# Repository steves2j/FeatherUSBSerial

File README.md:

# Feather USB Serial Big Fat Switch Edition
*FT232 USB serial port connection to RX/TX (Serial1) in an Adafruit FeatherWing form-factor*

This simple board allows easy access to Serial1, typically for debugging purposes. You insert it in a [Adafruit FeatherWing Doubler](https://www.adafruit.com/product/2890) or [Tripler](https://www.adafruit.com/product/3417) along with your device.

While it's no big deal to attach a [FT232 breakout](https://www.sparkfun.com/products/12731), the FeatherWing is nice and neat with no dangling wires.
Now with Big fat Mode and Reset buttons. No more fiddling trying to reset and DFU that Particle.

This post has all of the information you need to build your own. It's not available for purchase pre-built.

## What You Need

This is a somewhat advanced project mainly because the FT232 has a lot of pins, very close together. It's probably not practical to solder by hand, so you'll need a SMD reflow oven to do it effectively.

- Circuit boards (I order them from [OshPark](https://oshpark.com))
- Stencil (this board can be assembled without one, but I order them from [OshStencils](https://oshstencils.com))
- Solder paste
- Reflow oven (the inexpensive [T962](https://www.amazon.com/dp/B01LZYEF90/ref=dp_prsubs_1) works fine)
- Soldering iron (for the header pins)
- Regular solder

In the eagle directory are the .brd and .sch files for Eagle CAD. One of the reasons I like OshPark is that they accept the .brd files directly, instead of having to generate Gerber files. It costs US$9.00 with free shipping for 3 FeatherWing boards.

There's also a .lbr file with all of the parts in this project.

## BOM (Bill of Materials)

| Quantity | Item | Example |
| --- | --- | --- |
| 1 | 0.01 uF capacitor 0805 | [SAMSUNG CL21B103KCANNNC](https://www.digikey.com/product-detail/en/samsung-electro-mechanics/CL21B103KCANNNC/1276-1249-6-ND/3891763) |
| 2 | 0.1 uF capacitor 0805 | [SAMSUNG CL21B104KBFNNNE](https://www.digikey.co.nz/product-detail/en/samsung-electro-mechanics/CL21B104KBFNNNE/1276-1180-1-ND/3889266) |
| 1 | 4.7 uF capacitor 0805 | [Murata GRM21BR61H475KE51L](https://www.digikey.co.nz/product-detail/en/murata-electronics-north-america/GRM21BR61H475KE51L/490-10751-1-ND/5251349) |
| 1 | Ferrite Bead 40 ohm 0805 | [Laird MI0805K400R-10](https://www.digikey.com/products/en/filters/ferrite-beads-and-chips/841?k=MI0805K400R&k=&pkeyword=MI0805K400R&sv=0&pv7=2&pv1989=0&sf=0&quantity=&ColumnSort=0&page=1&pageSize=25) |
| 3 | 680 ohm resistor 1/8w 0805 | [Panasonic ERJ-6GEYJ681V](https://www.digikey.com/product-detail/en/panasonic-electronic-components/ERJ-6GEYJ681V/P680ACT-ND/90033) | 
| 2 | LED red 5mA 0603 | [Lite-On LTST-C193KRKT-5A](https://www.digikey.com/product-detail/en/lite-on-inc/LTST-C193KRKT-5A/160-1830-1-ND/2356251) |
| 1 | LED green 5mA 0603 | [Lite-On LTST-C193KGKT-5A](https://www.digikey.com/product-detail/en/lite-on-inc/LTST-C193KGKT-5A/160-1828-1-ND/2356247) |
| 1 | FT232RL USB serial | [FTDI FT232RL](https://www.digikey.com/product-detail/en/ftdi-future-technology-devices-international-ltd/FT232RL-REEL/768-1007-1-ND/1836402) |
| 1 | Micro USB B SMD | [Amphenol FCI 10118194-0001LF](https://www.digikey.com/products/en?keywords=609-4618-1-nd) |
| | Male header pins 0.1" | [Sullins PRPC040SAAN-RC](https://www.digikey.com/product-detail/en/PRPC040SAAN-RC/S1011EC-40-ND/2775214) |
| 1 | Tactile Switch Red | [TL3300CF260Q](https://www.digikey.co.nz/product-detail/en/e-switch/TL3300CF260Q/EG4905CT-ND/2498465) |
| 1 | Tactile Switch Blk | [TL3300CF160Q](https://www.digikey.co.nz/product-detail/en/e-switch/TL3300CF160Q/EG4904CT-ND/2498463) |

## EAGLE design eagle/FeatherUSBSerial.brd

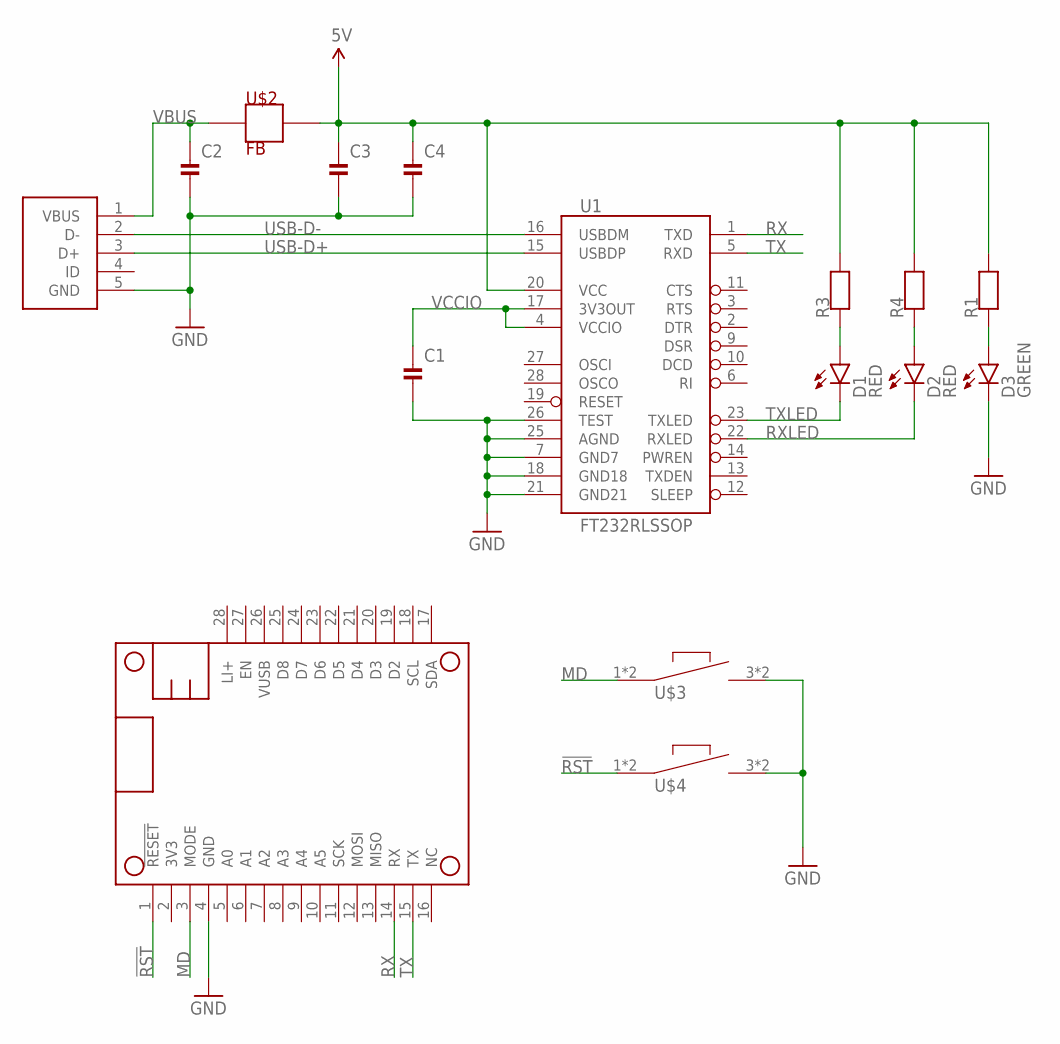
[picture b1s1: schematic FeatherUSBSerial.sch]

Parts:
C1, C3: 0.1uF; _0805MP
C2: 0.01uF; _0805MP
C4: 4.7uF; _0805MP
D1, D2: RED; LED-0603
D3: GREEN; LED-0603
MS1: FEATHERWING_NODIM
R1, R3, R4: 680; 0805-NO
U1: FT232RLSSOP; SSOP28DB
U$1: USB-MICRO-B-SOCKET-AMPHENOL; USB-B-SMT-AMPHENOL
U$2: FB; 0805
U$3, U$4: TL3300CFXXXQ; 12MM_TACTILE

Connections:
5V: C3.1, C4.1, R1.2, R3.2, R4.2, U1.20 (VCC), U$2.2
!RST: MS1.1 (!RESET), U$4.1, U$4.2
GND: C1.2, C2.2, C3.2, C4.2, D3.C, MS1.4 (GND), U1.7 (GND7), U1.18 (GND18), U1.21 (GND21), U1.25 (AGND), U1.26 (TEST), U$1.5 (GND), U$3.3, U$3.4, U$4.3, U$4.4
MD: MS1.3 (MODE), U$3.1, U$3.2
unnamed: D3.A, R1.1
unnamed: D1.A, R3.1
unnamed: D2.A, R4.1
RX: MS1.14 (RX), U1.1 (TXD)
RXLED: D2.C, U1.22 (RXLED)
TX: MS1.15 (TX), U1.5 (RXD)
TXLED: D1.C, U1.23 (TXLED)
USB-D+: U1.15 (USBDP), U$1.3 (D+)
USB-D-: U1.16 (USBDM), U$1.2 (D-)
VBUS: C2.1, U$1.1 (VBUS), U$2.1
VCCIO: C1.1, U1.4 (VCCIO), U1.17 (3V3OUT)

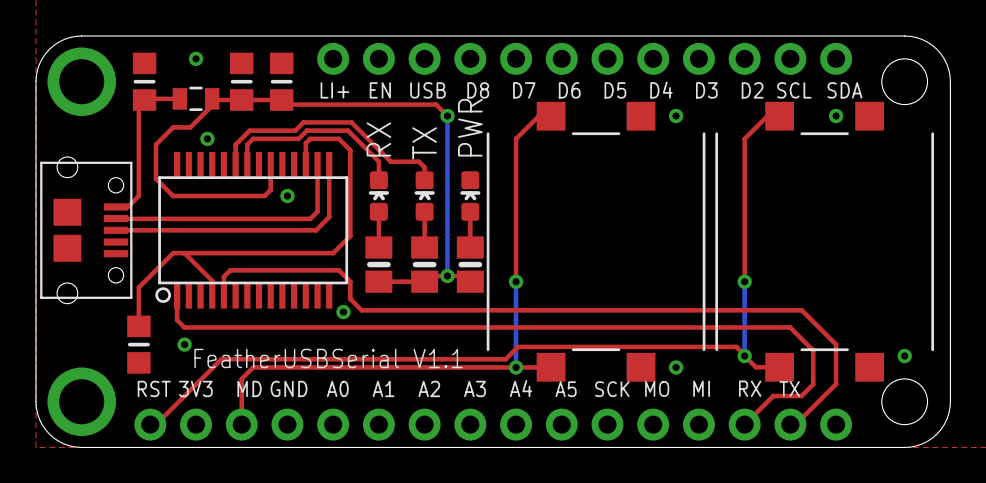
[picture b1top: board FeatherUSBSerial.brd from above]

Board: 2 copper layers, 50.8 x 22.9 mm, 16 parts (0 on the bottom side), 15 nets.

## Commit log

2019-03-21 Added Big Buttons
2019-03-21 Added updated schematic and board image
2019-03-21 Updated to use more common and easier to manipulate 0805 Cap's and Resistors.
2019-03-21 Ground loop fix
